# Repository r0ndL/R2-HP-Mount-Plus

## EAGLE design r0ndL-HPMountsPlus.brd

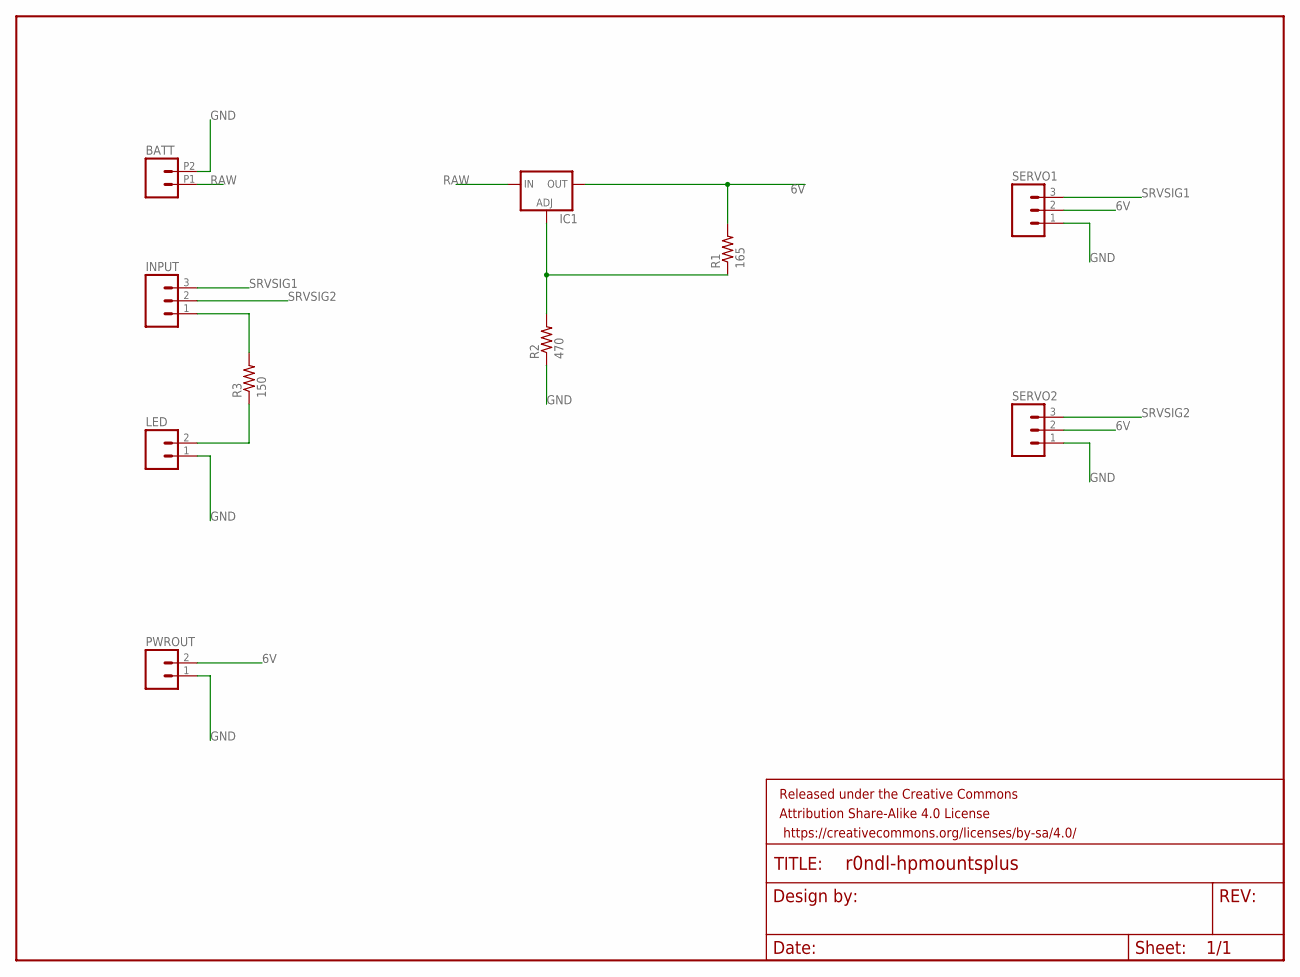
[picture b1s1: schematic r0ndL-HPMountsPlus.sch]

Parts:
BATT: M022.54MM_SCREWTERM; 1X02_2.54_SCREWTERM
FRAME1: FRAME-LETTER; CREATIVE_COMMONS
IC1: LM317TS; 317TS
INPUT: M03PTH; 1X03
LED: M02PTH; 1X02
PWROUT: M02PTH; 1X02
R1: 165; AXIAL-0.4
R2: 470; AXIAL-0.4
R3: 150; AXIAL-0.4
SERVO1, SERVO2: M03PTH; 1X03

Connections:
6V: IC1.2 (OUT), PWROUT.2, R1.P$2 (2), SERVO1.2, SERVO2.2
GND: BATT.P2 (2), LED.1, PWROUT.1, R2.P$1 (1), SERVO1.1, SERVO2.1
unnamed: IC1.1 (ADJ), R1.P$1 (1), R2.P$2 (2)
unnamed: LED.2, R3.P$1 (1)
unnamed: INPUT.1, R3.P$2 (2)
RAW: BATT.P1 (1), IC1.3 (IN)
SRVSIG1: INPUT.3, SERVO1.3
SRVSIG2: INPUT.2, SERVO2.3

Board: 2 copper layers, 11 parts (0 on the bottom side), 8 nets, no tracks yet.

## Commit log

2016-02-29 :lollipop: Added .gitattributes & .gitignore files
2016-02-29 Initial Upload

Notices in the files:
parts and their libraries:
SparkFun-Aesthetics: Licensing: Creative Commons ShareAlike 4.0 International - https://creativecommons.org/licenses/by-sa/4.0
SparkFun-Aesthetics: Released under the Creative Commons Attribution Share-Alike 4.0 License
SparkFun-Aesthetics: https://creativecommons.org/licenses/by-sa/4.0
